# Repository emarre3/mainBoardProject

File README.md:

This repo is to hold my kiCad files all in one place, as well as part documentation and other senior design files that I want to have handy.

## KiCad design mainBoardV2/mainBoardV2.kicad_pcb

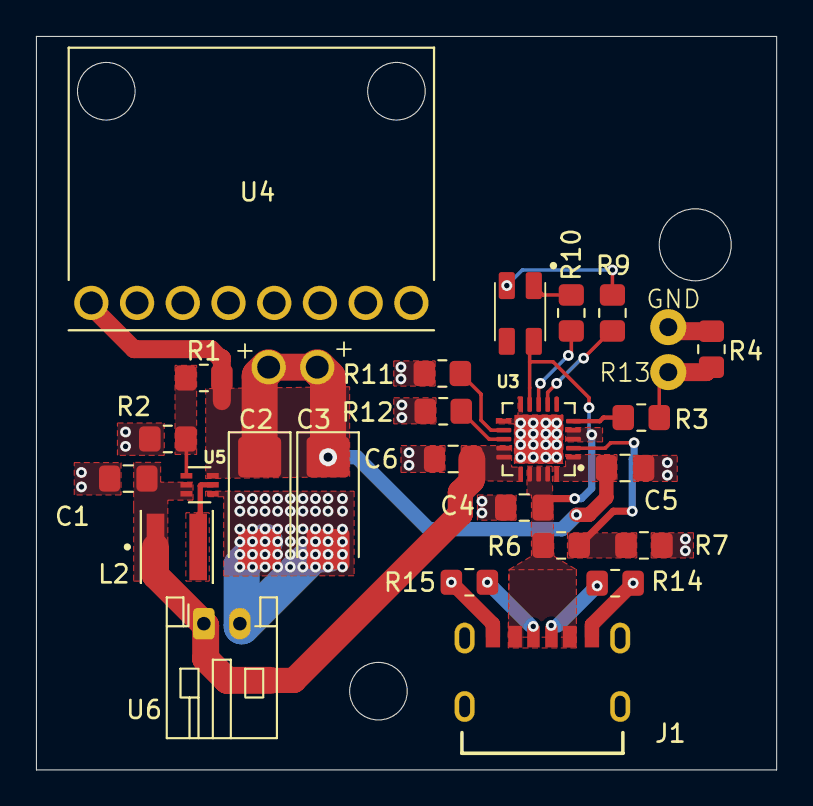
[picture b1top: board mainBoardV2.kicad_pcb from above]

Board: 2 copper layers, 41.1 x 40.7 mm, 26 parts (0 on the bottom side), 17 nets.

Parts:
C1, C4: 10uF; C_0805_2012Metric_Pad1.18x1.45mm_HandSolder
C2, C3: 22uF; CP_EIA-6032-15_Kemet-U_HandSolder
C5, C6: 4.7uF; C_0805_2012Metric_Pad1.18x1.45mm_HandSolder
J1: USB4125-GF-A_REVA2; GCT_USB4125-GF-A_REVA2
L2: XEL4030-102MEC; IND_XEL4030-102MEC
R1: 766k; R_0805_2012Metric_Pad1.20x1.40mm_HandSolder
R2, R11: 100k; R_0805_2012Metric_Pad1.20x1.40mm_HandSolder
R3: 1.5k; R_0805_2012Metric_Pad1.20x1.40mm_HandSolder
R4: 70k; R_0805_2012Metric_Pad1.20x1.40mm_HandSolder
R6: 330k; R_0805_2012Metric_Pad1.20x1.40mm_HandSolder
R7: 110k; R_0805_2012Metric_Pad1.20x1.40mm_HandSolder
R9: 160; R_0805_2012Metric_Pad1.20x1.40mm_HandSolder
R10: 300; R_0805_2012Metric_Pad1.20x1.40mm_HandSolder
R12: 2k; R_0805_2012Metric_Pad1.20x1.40mm_HandSolder
R13: 10k; 103AT-11_NTC_throughole
R14, R15: 5.1k; R_0805_2012Metric_Pad1.20x1.40mm_HandSolder
U3: MCP73871-2AAI_ML; QFN50P400X400X100-21N
U4: MPU6050_Module; MODULE_OC09600
U5: TPS61023DRLT; SOT50P160X60-6N
U6: JST_PH_S2B-PH-K_1x02_P2.00mm_Horizontal
U7: BivarSMTL-SRGY

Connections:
+5V: C4.1, J1.A9 (VBUS), J1.B9 (VBUS), R6.1, U3.3 (SEL), U3.4 (PROG2), U3.9 (~TE), U3.17 (CE), U3.18 (IN), U3.19 (IN), U7.4 (Common_Anode)
/Boost FB: R1.2, R2.2, U5.1 (FB)
/ChargeDone: R9.1, U3.7 (STAT2)
/LowBatt: R10.1, U3.8 (STAT1/*LBO)
/PROG1: R12.1, U3.13 (PROG1)
/PROG3: R11.2, U3.12 (PROG3)
/SW: L2.2, U5.5 (SW)
/Therm: R3.1, U3.5 (THERM)
/VBatt+: C1.1, C6.1, L2.1, U3.14 (VBAT), U3.15 (VBAT), U3.16 (VBAT_SENSE), U5.2 (EN), U5.3 (VIN), U6.1 (VBAT+)
/VPCC: R6.2, R7.1, U3.2 (VPCC)
/VoutBoost: C2.1, C3.1, C5.1, R1.1, U3.1 (OUT), U3.20 (OUT), U4.VCC, U5.6 (VOUT)
GND: C1.2, C2.2, C3.2, C4.2, C5.2, C6.2, J1.A12 (GND), J1.B12 (GND), J1.S1 (SHIELD), J1.S2 (SHIELD), J1.S3 (SHIELD), J1.S4 (SHIELD), R2.1, R4.2, R7.2, R11.1, R12.2, R13.1, R14.2, R15.2, U3.10 (VSS), U3.11 (VSS), U3.21 (EP), U4.GND, U5.4 (GND), U6.2 (VBAT-)
unnamed: J1.A5 (CC1), R15.1
unnamed: J1.B5 (CC2), R14.1
unnamed: R3.2, R4.1, R13.2
unnamed: R9.2, U7.1 (Green)
unnamed: R10.2, U7.3 (Red)

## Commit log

2026-02-27 Adding battery documentation to docs folder
2026-02-27 test
2026-02-28 2.28.26.C1
2026-02-28 2.28.28.C2
2026-03-01 2.28.26.C3
2026-03-01 2.28.26.C4
2026-03-01 2.28.26.C5
2026-03-01 end of 2.28.26 session
2026-03-01 3.1.26.C2
    Have a preliminary layout, ready to perfect
2026-03-01 3.1.26.C3
    Done for the day?
2026-03-02 3.2.26.C1
2026-03-02 3.2.26.C2
    Q&A with Ricardo
2026-03-07 3.6.26.C1
    Wanted to start, but ended this session early
2026-03-08 3.7.26.C1
    removed the old boost converter chip and circuit and put in the new one. Unconnected.
2026-03-09 3.9.26.C1
    Closing prior session to move to laptop
2026-03-10 3.9.26.Cf
    Closing the 3.9 session as it ran into 3.10. boost circuit ready to be optimally connected.
    Charger ready for a fresh start.
    Warning about 3 unconnected vias currently. Don't see them yet.
2026-03-11 3.11.26.C1
    False Start
2026-03-11 3.11.26.C2
    Connected nets on booster. Still need to create ground vias
2026-03-11 3.11.26.C2
    Connected up the capacitors in the charging circuit.
2026-03-11 3.11.26.C3
    Post meeting with Deepika and some group discussion, removing ESP32 from schemactic and breadboard. Moved some components closer together to get a rough estimate for board size so we can start design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
2026-03-12 3.11.26.C4
    Finalized copper connections and placed ground vias. Got closer to final size goal of 50x50 mm (2x2in). Placed ground vias, and placed thick traces on power connections.
2026-03-12 3.12.26.C1
    Seems this board is close to done. Need to discuss where our pushbutton and on/of switch would connect.
2026-03-13 x
    forced to commit
2026-03-16 3.16.23.C1
    Rotated IMU for a more compact design, per Connor's suggestion
2026-03-17 3.17.26.C1
    inserted a true NTC thermistor, set to operate from 0 to 50C. Added two Vout vias for use with the board outside of the connection to the IMU. Add through holes to feed jst wires or the NTC bead thro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
2026-03-18 3.17.26.C2
    Added tantalum capacitors to output of boost converter. Have created gerber and drill files after running DRC check until only thing left were some clearance warnings. manufacturer can handle.
2026-03-23 3.22.26.C1
    Added replacement inductor footprint and symbol to library. Updated board and schematic files with new component, but now gerber job files are not coming out correctly. Look transparent in a Gerber V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
2026-03-23 Revert "3.22.26.C1"
    This reverts commit 781c2ef683714b83309e94a3ccc7edb13d8085a7.
2026-03-23 3.23.26.C1
    Revert all my last changes. Realized I could use the original footprint of my old inductor, and the length the paths is the only thing that changes, by 0.3mm. Nothing had to move! And the fabrication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
2026-04-07 3
    d
2026-05-08 Minor file cleanup
    Removed files that do not directly relate to the final board project
2026-05-08 Closing project on laptop.
    Not closing this commit first before opening project on another device created a branch
